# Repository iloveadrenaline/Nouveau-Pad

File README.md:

# Nouveau-Pad ⚡

A 4-key  built by me  on a Seeed XIAO RP2040. Submitted to Hack Club's **Hackpad** You Ship, We Ship program.

---

## Overview

**Nouveau Pad** is a compact macropad designed around the Seeed XIAO RP2040. It has 4 keys that are programmable into whatever you like , I made this project so I can change my volume with the encoder because I'm tired to go into Windows Control Panel thing , Linux is better btw. Overall , I hope you like the project
**Project link** : https://stardance.hackclub.com/projects/39690

## Features

-4 Mechanical Switches

-0.91 inch oled screen for displaying cool stuff

-An encoder to change the volume because why not

-A window so you can see the pcb because it looks cool

## PCB Schematics

## Bill of Materials (BOM)

1x Seeed XIAO RP2040

1x 0.91 inch OLED display

4x MX-Style switches

1x EC11 Rotary encoder

6x SK6812 MINI-E LEDs

4x white blank DSA keycaps

4x M3 heatset inserts

4x M3 screws

## Firmware
The firmware is made in CircuitPython that's all I can tell you , I'm very begginer to this so you can just Google it . Psst I recommend Claude 

## Repository Structure

```
Nouveau-Pad/
├── README.md
├── LICENSE
├── cad/
│   ├── nouveaupad.step        # full assembly
│   └── nouveaupad.stl
├── pcb/
│   ├── nouveaupad.kicad_pro
│   ├── nouveaupad.kicad_sch
│   ├── nouveaupad.kicad_pcb
│   └── gerbers/
└── firmware/
│   ├── README.md
│   └── KMK/
│
└── production/
    ├──KMK
    ├──Case_Bottom.stl
    ├──Case_Top.stl
    ├──Gerbers.zip
    └──Knob.stl

```

## Assembly

1. Order PCB  via JLCPCB or PCBWay using the Gerber
2. Solder U1 (XIAO RP2040), U2 (OLED), SW1–SW5, and D1–D6 in that order (MCU → display → switches → LEDs).
3. Flash firmware from `firmware/KMK/` onto the controller
4. 3D print the case parts
5. Heat-set M3 inserts, assemble top/bottom with screws, snap in keycaps.

## License

This project is released under the MIT License -- see in the repo

## Credits

- Built for [Hack Club's Hackpad](https://hackpad.hackclub.com) YSWS program
- MX switch / XIAO / SK6812 footprints from the Hackpad KiCad starter library
- Designed by [iloveadrenaline](https://github.com/iloveadrenaline)
- The KMK software was made with minimal use of Antrophic Claude
  Peace out
- Honorable mention to [Tensor](https://github.com/TensorSwe) , he guided me and made this project a reality

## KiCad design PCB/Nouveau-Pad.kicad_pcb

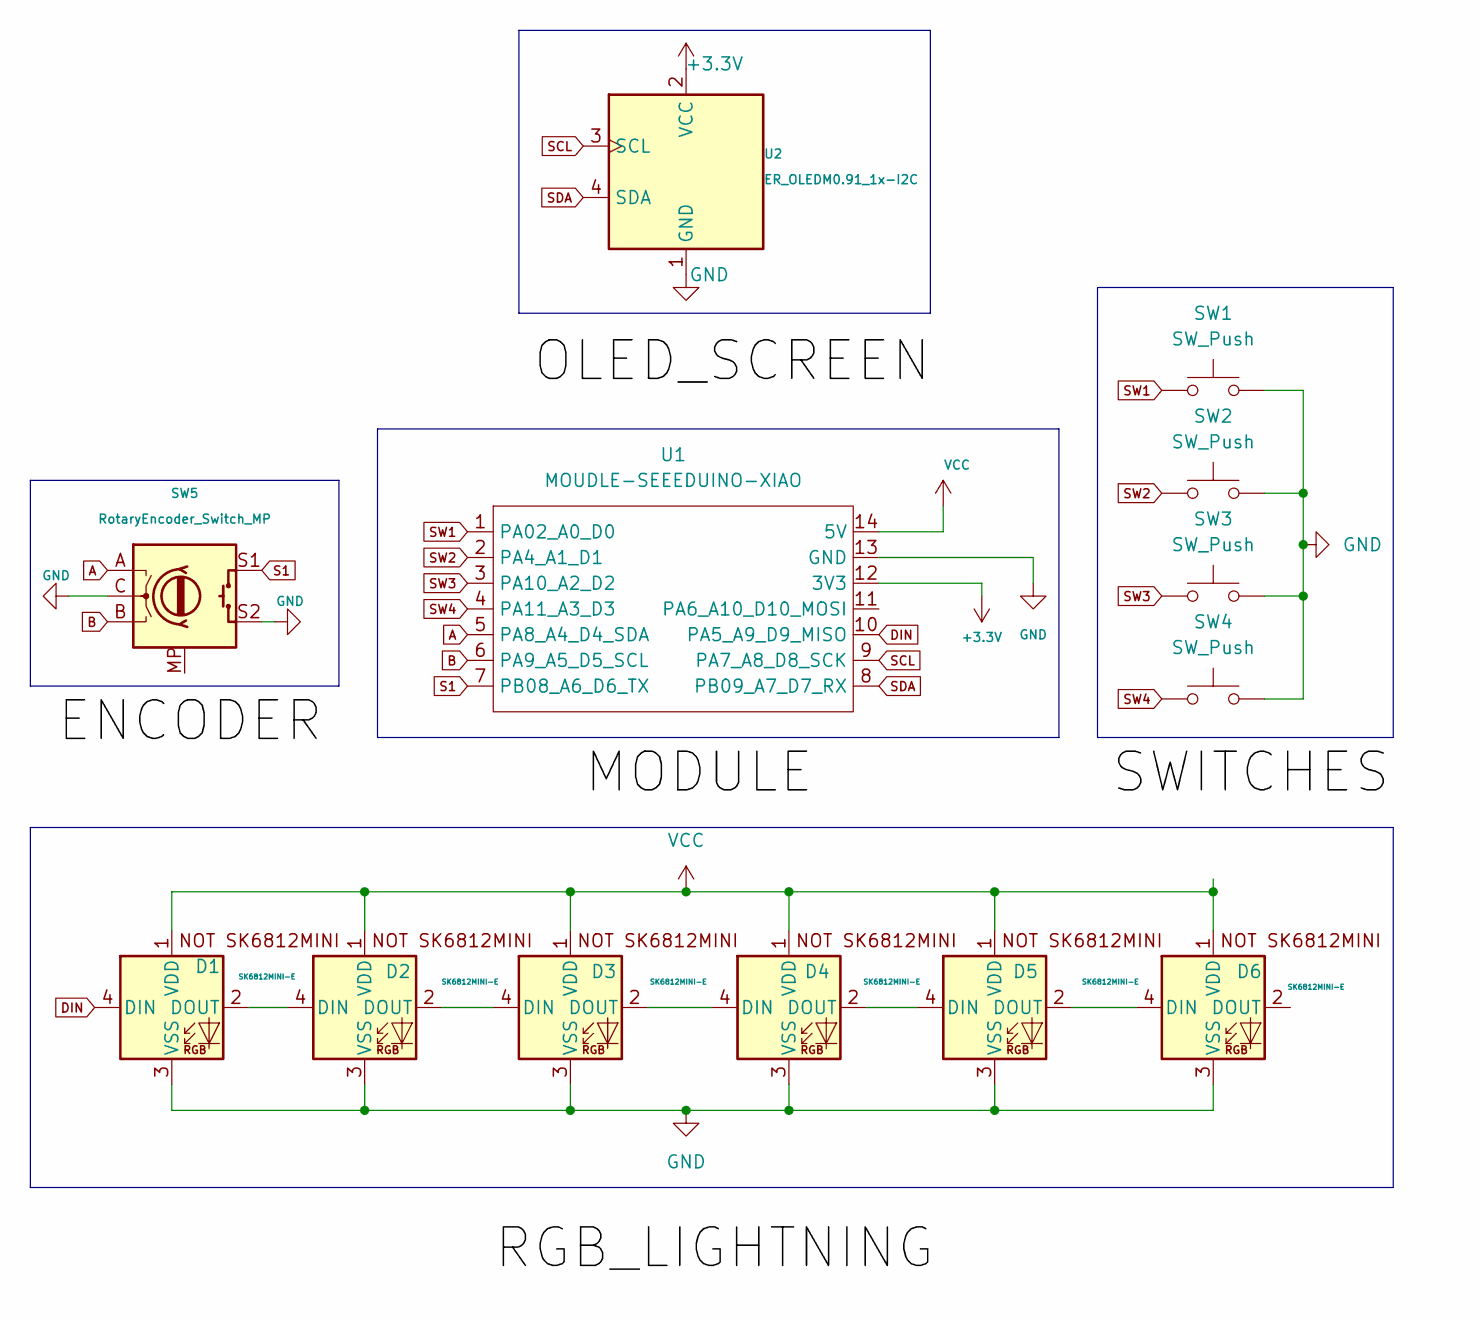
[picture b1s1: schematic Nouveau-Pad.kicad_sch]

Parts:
D1, D2, D3, D4, D5, D6: SK6812MINI-E; SK6812MINI-E_fixed
SW1, SW2, SW3, SW4: SW_Push; SW_Cherry_MX_1.00u_PCB
SW5: RotaryEncoder_Switch_MP; RotaryEncoder_Alps_EC11E-Switch_Vertical_H20mm
U1: MOUDLE-SEEEDUINO-XIAO; XIAO-Generic-Hybrid-14P-2.54-21X17.8MM
U2: ER_OLEDM0.91_1x-I2C

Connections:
+3.3V: U1.12 (3V3), U2.2 (VCC)
A: SW5.A, U1.5 (PA8_A4_D4_SDA)
B: SW5.B, U1.6 (PA9_A5_D5_SCL)
DIN: D1.4 (DIN), U1.10 (PA5_A9_D9_MISO)
GND: D1.3 (VSS), D2.3 (VSS), D3.3 (VSS), D4.3 (VSS), D5.3 (VSS), D6.3 (VSS), SW1.2, SW2.2, SW3.2, SW4.2, SW5.C, SW5.S2, U1.13 (GND), U2.1 (GND)
unnamed: D1.2 (DOUT), D2.4 (DIN)
unnamed: D2.2 (DOUT), D3.4 (DIN)
unnamed: D3.2 (DOUT), D4.4 (DIN)
unnamed: D4.2 (DOUT), D5.4 (DIN)
unnamed: D5.2 (DOUT), D6.4 (DIN)
S1: SW5.S1, U1.7 (PB08_A6_D6_TX)
SCL: U1.9 (PA7_A8_D8_SCK), U2.3 (SCL)
SDA: U1.8 (PB09_A7_D7_RX), U2.4 (SDA)
SW1: SW1.1, U1.1 (PA02_A0_D0)
SW2: SW2.1, U1.2 (PA4_A1_D1)
SW3: SW3.1, U1.3 (PA10_A2_D2)
SW4: SW4.1, U1.4 (PA11_A3_D3)
VCC: D1.1 (VDD), D2.1 (VDD), D3.1 (VDD), D4.1 (VDD), D5.1 (VDD), D6.1 (VDD), U1.14 (5V)

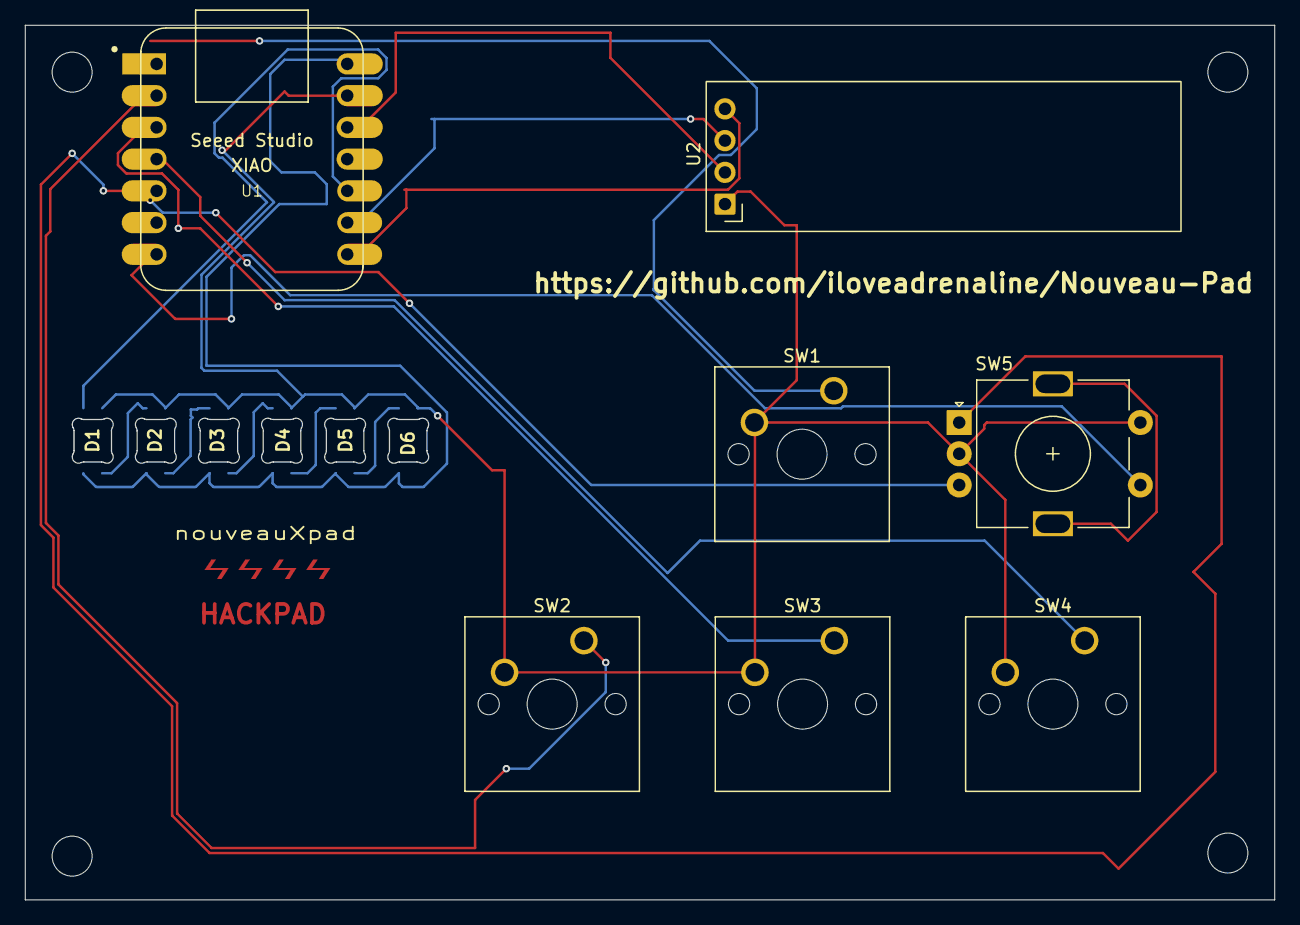
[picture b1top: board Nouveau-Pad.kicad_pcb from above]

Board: 2 copper layers, 100.0 x 70.0 mm, 13 parts (0 on the bottom side), 18 nets.
